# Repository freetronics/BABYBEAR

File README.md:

Freetronics Baby Bear
=====================
Copyright 2013-2018 Freetronics Pty Ltd  <www.freetronics.com>  

The Baby Bear is an Arduino Compatible Board based on the ATmega1284P
MCU, which means it's compatible with projects designed for the Arduino
Uno but has more memory and I/O capabilities.

Features:

 * USB-C connector
 * Prototyping area
 * LEDs visible on the edge when a shield is fitted
 * Overlay guide where you need it (both top and bottom)
 * D13 pin works for everything
 * Mounting holes and power pads
 * All connections in the same place

You can find more information at:

  http://www.freetronics.com.au/babybear

INSTALLATION
------------
The design is saved as an EAGLE project. EAGLE PCB design software is
available from www.cadsoftusa.com free for non-commercial use. To use
this project download it and place the directory containing these files
into the "eagle" directory on your computer. Then open EAGLE and
navigate to the project.

INSTALLATION
------------
The design is saved as an EAGLE project. EAGLE PCB design software is
available from www.cadsoftusa.com free for non-commercial use. To use
this project download it and place the directory containing these files
into the "eagle" directory on your computer.

DISTRIBUTION
------------
The specific terms of distribution of this project are governed by the
license referenced below.

LICENSE
-------
Licensed under the TAPR Open Hardware License (www.tapr.org/OHL).
The "license" folder within this repository also contains a copy of
this license in plain text format.

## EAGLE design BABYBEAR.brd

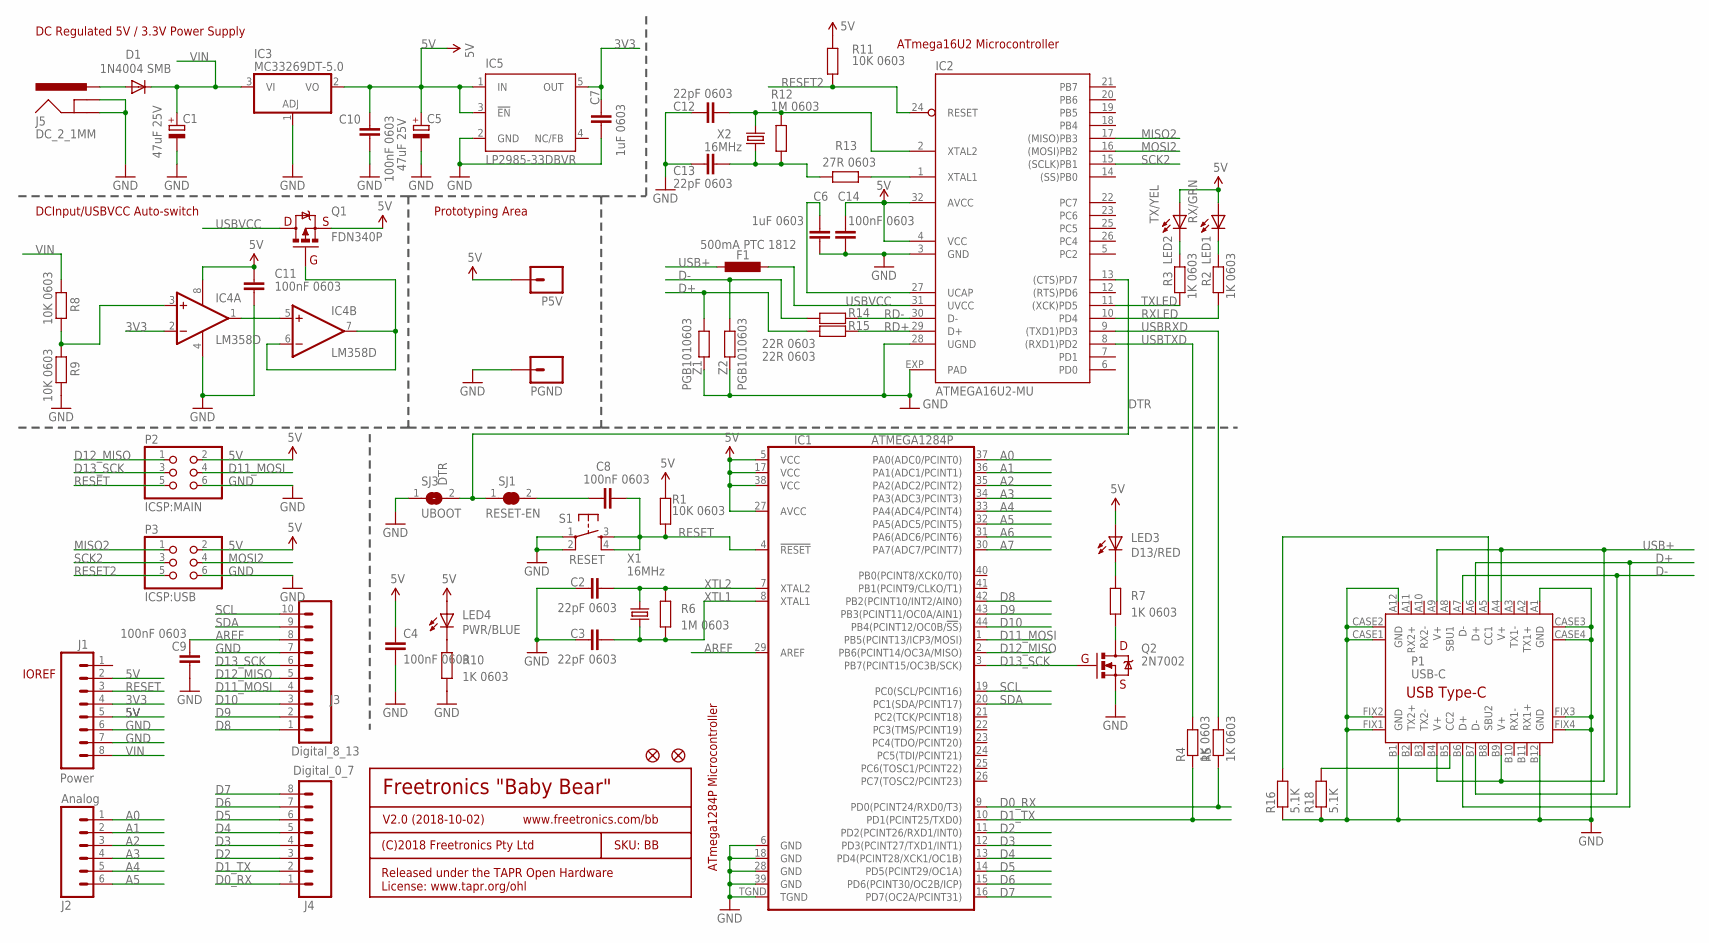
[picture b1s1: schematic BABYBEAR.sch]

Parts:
C1, C5: 47uF 25V; PANASONIC_D
C2, C3, C12, C13: 22pF 0603; 0603
C4, C8, C9, C10, C11, C14: 100nF 0603; 0603
C6, C7: 1uF 0603; 0603
D1: 1N4004 SMB; SMB-DIODE
F1: 500mA PTC 1812; L1812
IC1: ATMEGA1284P; QFN-44M1
IC2: ATMEGA16U2-MU; ATMEL_QFN32
IC3: MC33269DT-5.0; DPACK
IC4: LM358D; SO08
IC5: LP2985-33DBVR; TEXAS_SOT23-DBV
J1: Power; 1X08
J2: Analog; 1X06
J3: Digital_8_13; 1X10
J4: Digital_0_7; 1X08
J5: DC_2_1MM; POWER_JACK_PTH_SLOTS
LED1: RX/GRN; LED-0603
LED2: TX/YEL; LED-0603
LED3: D13/RED; LED-0603
LED4: PWR/BLUE; LED-0603
P1: USB-C; USB-C-U52A
P2: ICSP:MAIN; 2X03
P3: ICSP:USB; 2X03
P5V: M01SMD; LUXEON-PAD
PGND: M01SMD; LUXEON-PAD
Q1: FDN340P; SOT23
Q2: 2N7002; SOT23-3
R1, R8, R9, R11: 10K 0603; 0603
R2, R3, R4, R5, R7, R10: 1K 0603; 0603
R6, R12: 1M 0603; 0603
R13: 27R 0603; 0603
R14, R15: 22R 0603; 0603
R16, R18: 5.1K; 0603
S1: RESET; TACTILE_SWITCH_SMD
SJ1: RESET-EN; SJC
SJ3: UBOOT; SJ
U$5, U$14: FIDUCIAL1X2.5; FIDUCIAL-1X2.5
X1, X2: 16MHz; HC49U-V
Z1, Z2: PGB1010603; 0603

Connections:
3V3: C7.2, IC4.2 (-IN), IC5.5 (OUT), J1.4
5V: C4.1, C5.+, C10.1, C11.1, C14.1, IC1.5 (VCC), IC1.17 (VCC), IC1.27 (AVCC), IC1.38 (VCC), IC2.4 (VCC), IC2.32 (AVCC), IC3.2 (VO), IC4.8 (V+), IC5.1 (IN), IC5.3 (!EN), J1.2, J1.5, LED1.A, LED2.A, LED3.A, LED4.A, P2.2, P3.2, P5V.P$1, Q1.2 (S), R1.2, R11.2
A0: IC1.37 (PA0(ADC0/PCINT0)), J2.1
A1: IC1.36 (PA1(ADC1/PCINT1)), J2.2
A2: IC1.35 (PA2(ADC2/PCINT2)), J2.3
A3: IC1.34 (PA3(ADC3/PCINT3)), J2.4
A4: IC1.33 (PA4(ADC4/PCINT4)), J2.5
A5: IC1.32 (PA5(ADC5/PCINT5)), J2.6
A6: IC1.31 (PA6(ADC6/PCINT6))
A7: IC1.30 (PA7(ADC7/PCINT7))
AREF: C9.1, IC1.29 (AREF), J3.8
D0_RX: IC1.9 (PD0(PCINT24/RXD0/T3)), J4.1, R5.1
D1_TX: IC1.10 (PD1(PCINT25/TXD0)), J4.2, R4.1
D2: IC1.11 (PD2(PCINT26/RXD1/INT0)), J4.3
D3: IC1.12 (PD3(PCINT27/TXD1/INT1)), J4.4
D4: IC1.13 (PD4(PCINT28/XCK1/OC1B)), J4.5
D5: IC1.14 (PD5(PCINT29/OC1A)), J4.6
D6: IC1.15 (PD6(PCINT30/OC2B/ICP)), J4.7
D7: IC1.16 (PD7(OC2A/PCINT31)), J4.8
D8: IC1.42 (PB2(PCINT10/INT2/AIN0)), J3.1
D9: IC1.43 (PB3(PCINT11/OC0A/AIN1)), J3.2
D10: IC1.44 (PB4(PCINT12/OC0B/!SS!)), J3.3
D11_MOSI: IC1.1 (PB5(PCINT13/ICP3/MOSI)), J3.4, P2.4
D12_MISO: IC1.2 (PB6(PCINT14/OC3A/MISO)), J3.5, P2.1
D13_SCK: IC1.3 (PB7(PCINT15/OC3B/SCK)), J3.6, P2.3, Q2.1 (G)
D+: P1.A6 (D+), P1.B6 (D+), R15.2, Z1.1
D-: P1.A7 (D-), P1.B7 (D-), R14.2, Z2.1
DTR: IC2.13 ((CTS)PD7), SJ1.1, SJ3.2
GND: C1.-, C2.1, C3.1, C4.2, C5.-, C6.2, C7.1, C9.2, C10.2, C11.2, C12.1, C13.1, C14.2, IC1.6 (GND), IC1.18 (GND), IC1.28 (GND), IC1.39 (GND), IC1.TGND, IC2.3 (GND), IC2.28 (UGND), IC2.EXP (PAD), IC3.1 (ADJ), IC4.4 (V-), IC5.2 (GND), J1.6, J1.7, J3.7, J5.GND, J5.GNDBREAK, P1.A1 (GND), P1.A12 (GND), P1.B1 (GND), P1.B12 (GND), P1.CASE1 (GND), P1.CASE2 (GND), P1.CASE3 (GND), P1.CASE4 (GND), P1.FIX1 (GND), P1.FIX2 (GND), P1.FIX3 (GND), P1.FIX4 (GND), P2.6, P3.6, PGND.P$1, Q2.2 (S), R9.1, R10.1, R16.1, R18.1, S1.1, S1.2, SJ3.1, Z1.2, Z2.2
MISO2: IC2.17 ((MISO)PB3), P3.1
MOSI2: IC2.16 ((MOSI)PB2), P3.4
unnamed: C8.1, SJ1.2
unnamed: IC2.1 (XTAL1), R13.1
unnamed: P1.B5 (CC2), R18.2
unnamed: LED3.C, R7.2
unnamed: Q2.3 (D), R7.1
unnamed: P1.A5 (CC1), R16.2
unnamed: D1.A, J5.PWR
unnamed: IC4.3 (+IN), R8.1, R9.2
unnamed: IC4.1 (OUT), IC4.5 (+IN)
unnamed: LED1.C, R2.2
unnamed: IC4.6 (-IN), IC4.7 (OUT), Q1.1 (G)
unnamed: LED2.C, R3.2
unnamed: LED4.C, R10.2
unnamed: C12.2, IC2.2 (XTAL2), R12.2, X2.2
unnamed: C13.2, R12.1, R13.2, X2.1
unnamed: C6.1, IC2.27 (UCAP)
RD+: IC2.29 (D+), R15.1
RD-: IC2.30 (D-), R14.1
RESET: C8.2, IC1.4 (!RESET), J1.3, P2.5, R1.1, S1.3, S1.4
RESET2: IC2.24 (RESET), P3.5, R11.1
RXLED: IC2.10 (PD4), R2.1
SCK2: IC2.15 ((SCLK)PB1), P3.3
SCL: IC1.19 (PC0(SCL/PCINT16)), J3.10
SDA: IC1.20 (PC1(SDA/PCINT17)), J3.9
TXLED: IC2.11 ((XCK)PD5), R3.1
USB+: F1.1, P1.A4 (V+), P1.A9 (V+), P1.B4 (V+), P1.B9 (V+)
USBRXD: IC2.9 ((TXD1)PD3), R5.2
USBTXD: IC2.8 ((RXD1)PD2), R4.2
USBVCC: F1.2, IC2.31 (UVCC), Q1.3 (D)
VIN: C1.+, D1.C, IC3.3 (VI), J1.8, R8.2
XTL1: C3.2, IC1.8 (XTAL1), R6.1, X1.1
XTL2: C2.2, IC1.7 (XTAL2), R6.2, X1.2

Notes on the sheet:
Prototyping Area
DCInput/USBVCC Auto-switch
DC Regulated 5V / 3.3V Power Supply
ATmega16U2 Microcontroller
Freetronics "Baby Bear"
V2.0 (2018-10-02)
SKU: BB
(C)2018 Freetronics Pty Ltd
Released under the TAPR Open Hardware License: www.tapr.org/ohl
www.freetronics.com/bb
IOREF
ATmega1284P Microcontroller

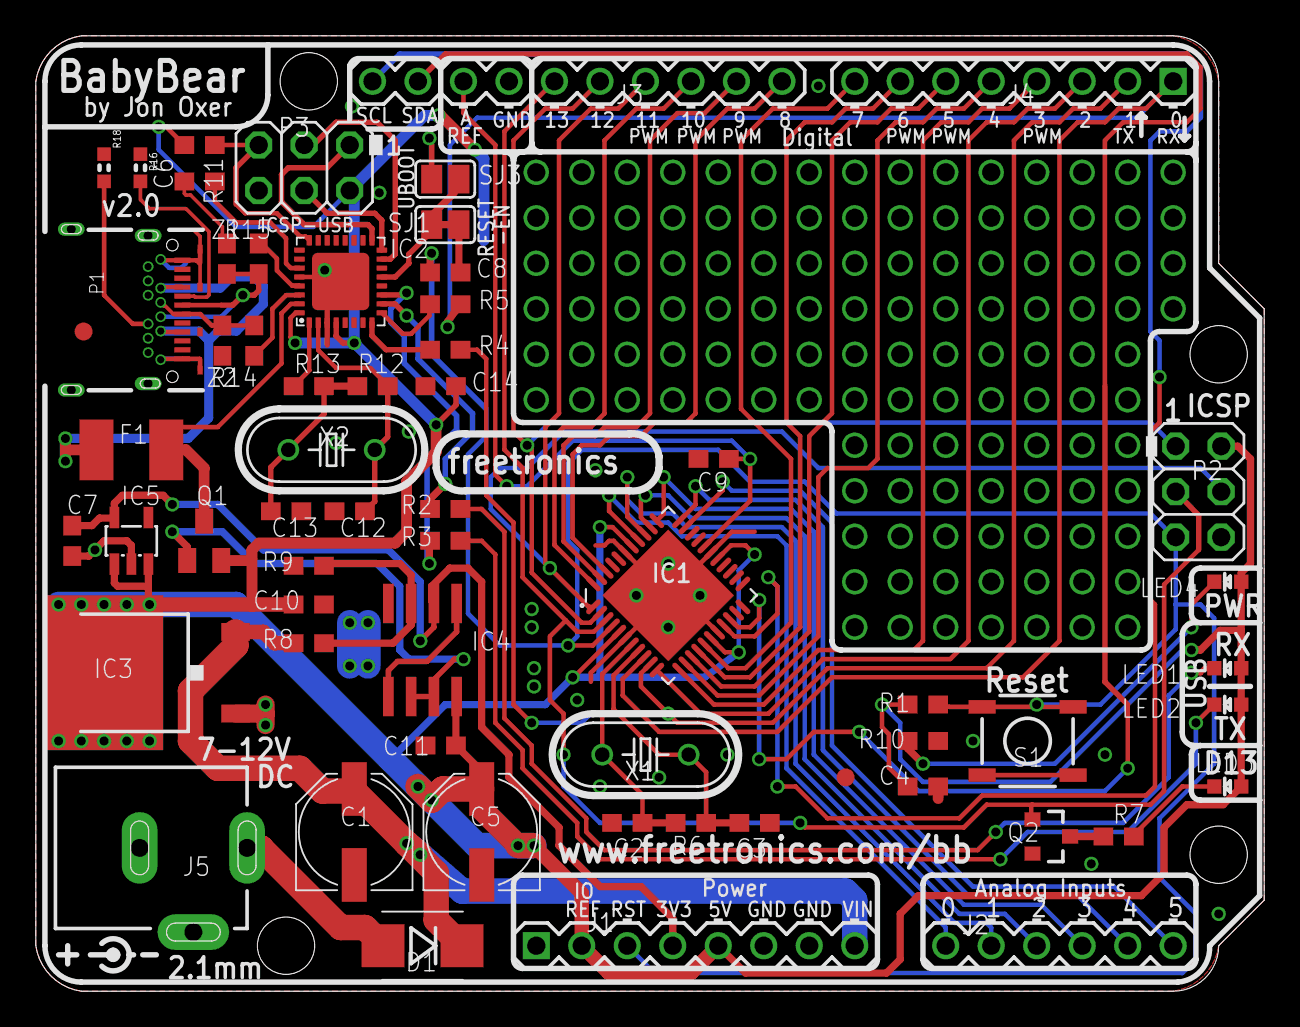
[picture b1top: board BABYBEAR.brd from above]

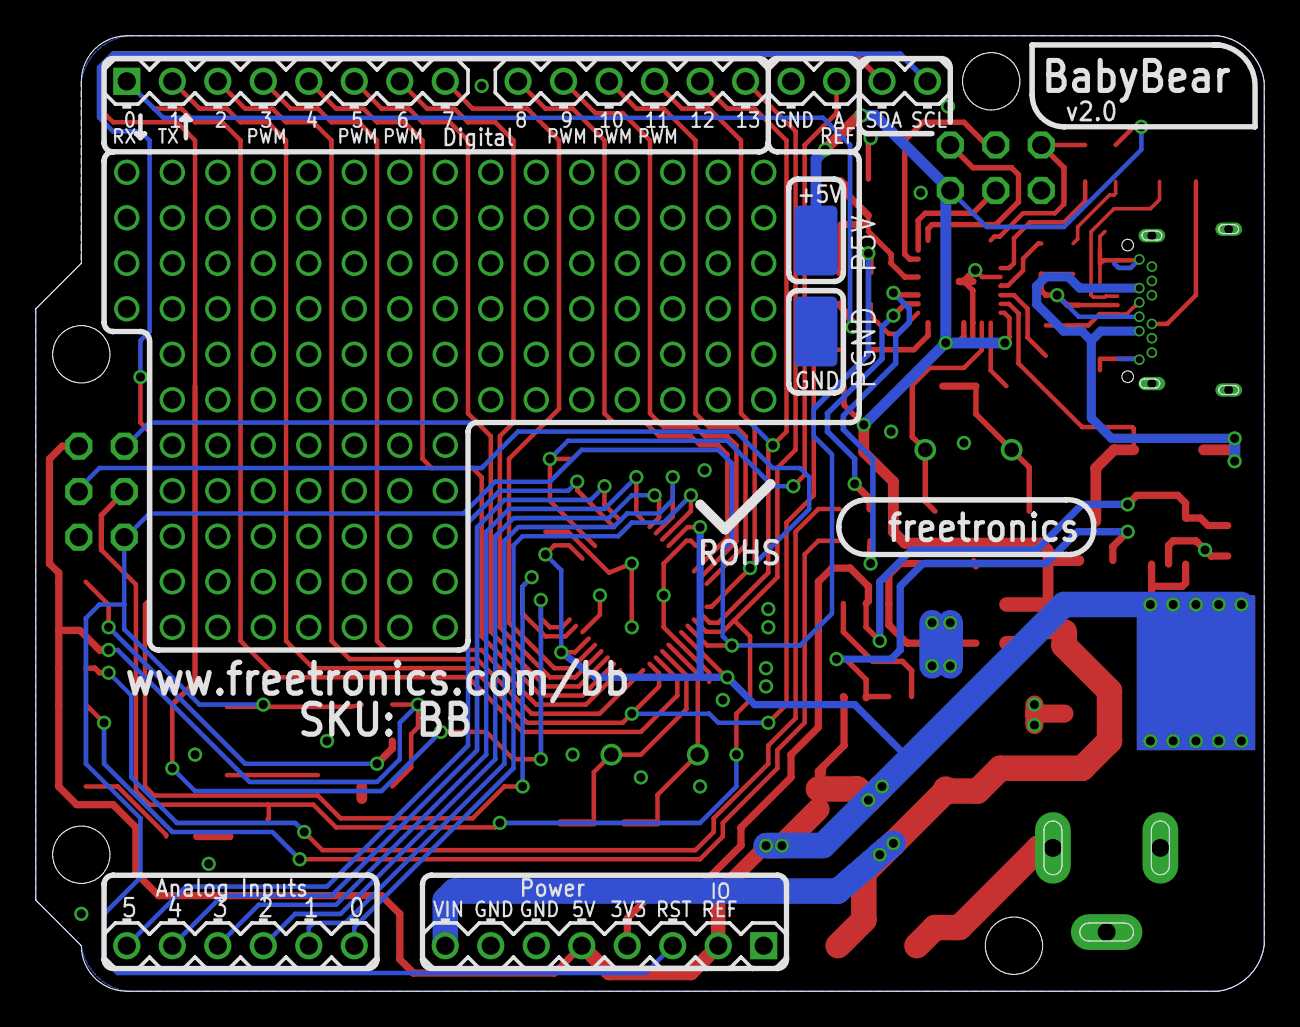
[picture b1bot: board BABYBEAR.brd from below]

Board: 2 copper layers, 68.6 x 53.3 mm, 63 parts (2 on the bottom side), 61 nets.

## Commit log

2018-03-27 Import of old project
2018-11-04 Changed USB connector to USB-C for v2.0 release

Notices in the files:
parts and their libraries:
freetronics-original: Licensing: CC v3.0 Share-Alike You are welcome to use this library for commercial purposes.
